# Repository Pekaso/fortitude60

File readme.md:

# Fortitude60

👊A 60% (12x5) split keyboard with staggerd column layout.👊

# Build Guide

## Fortitude60 v1.0(C94 Limited Edition)
[ビルドガイド（日本語）](Documents/buildguide_jp_v1.0.md)

[Build Guide (EN)](Documents/buildguide_en_v1.0.md)

## Fortitude60 v1.1(Yushakobo Ver.)
[ビルドガイド（日本語）](Documents/buildguide_jp_v1.1.md)

[Build Guide (EN)](Documents/buildguide_en_v1.1.md)

[Changes](https://github.com/Pekaso/fortitude60/issues/9)

# Firmware Flashing
[ファームウェア書き込み方法（日本語）](Documents/firmware_flashing-jp_new.md)

[Firmware Flashing（EN）](Documents/firmware_flashing-en_new.md)

## F.A.Q
[よくある質問（日本語）](Documents/faq_jp.md)

[Frequently Asked Questions（EN）](Documents/faq_en.md)

# License

Released under the MIT license. see [LICENSE](https://github.com/Pekaso/fortitude60/blob/master/LICENSE)

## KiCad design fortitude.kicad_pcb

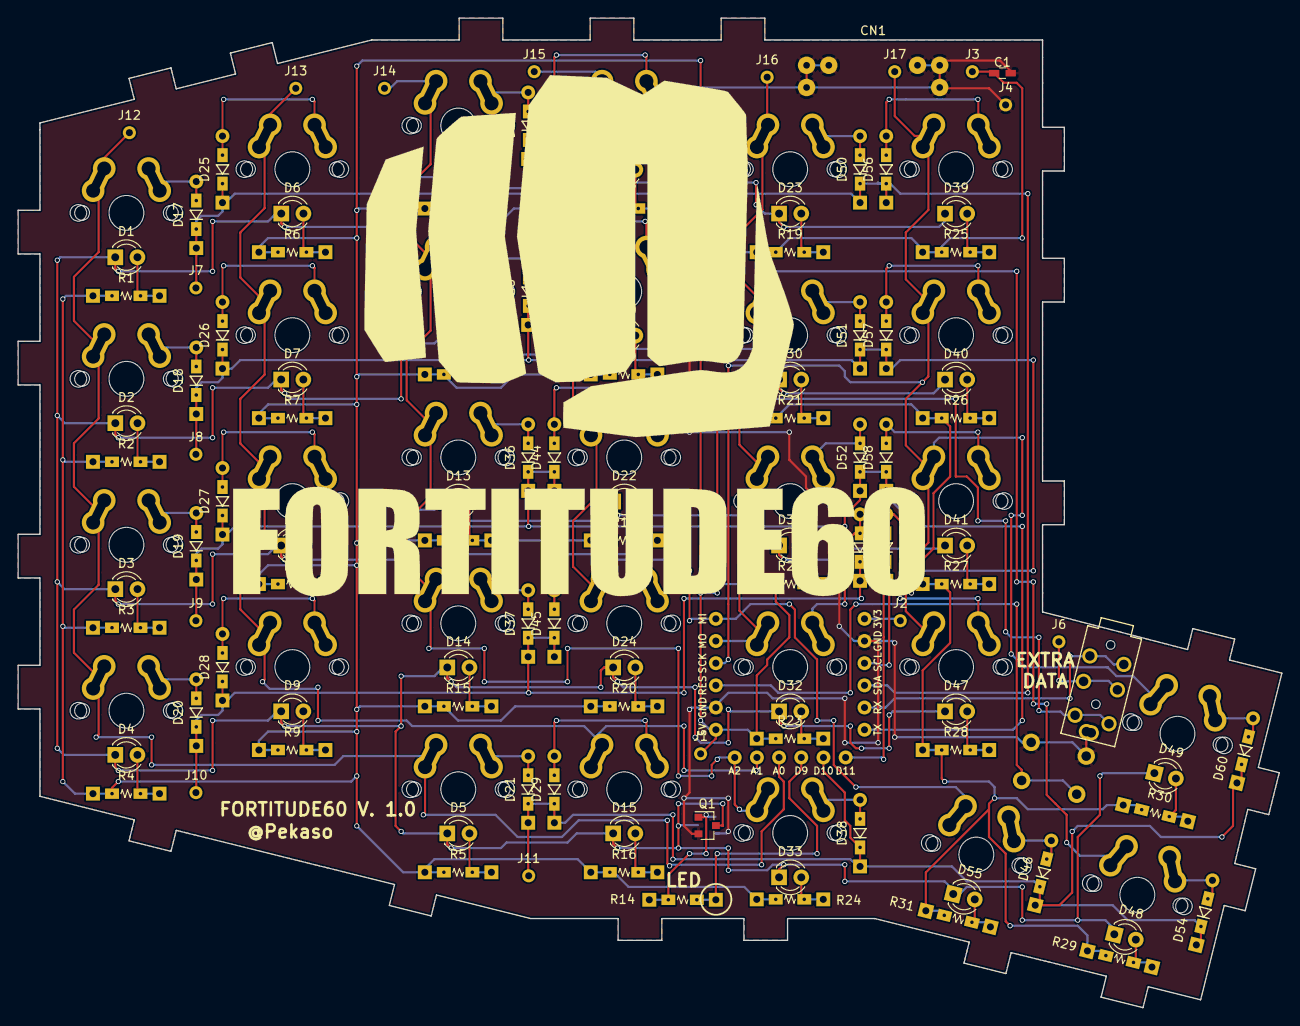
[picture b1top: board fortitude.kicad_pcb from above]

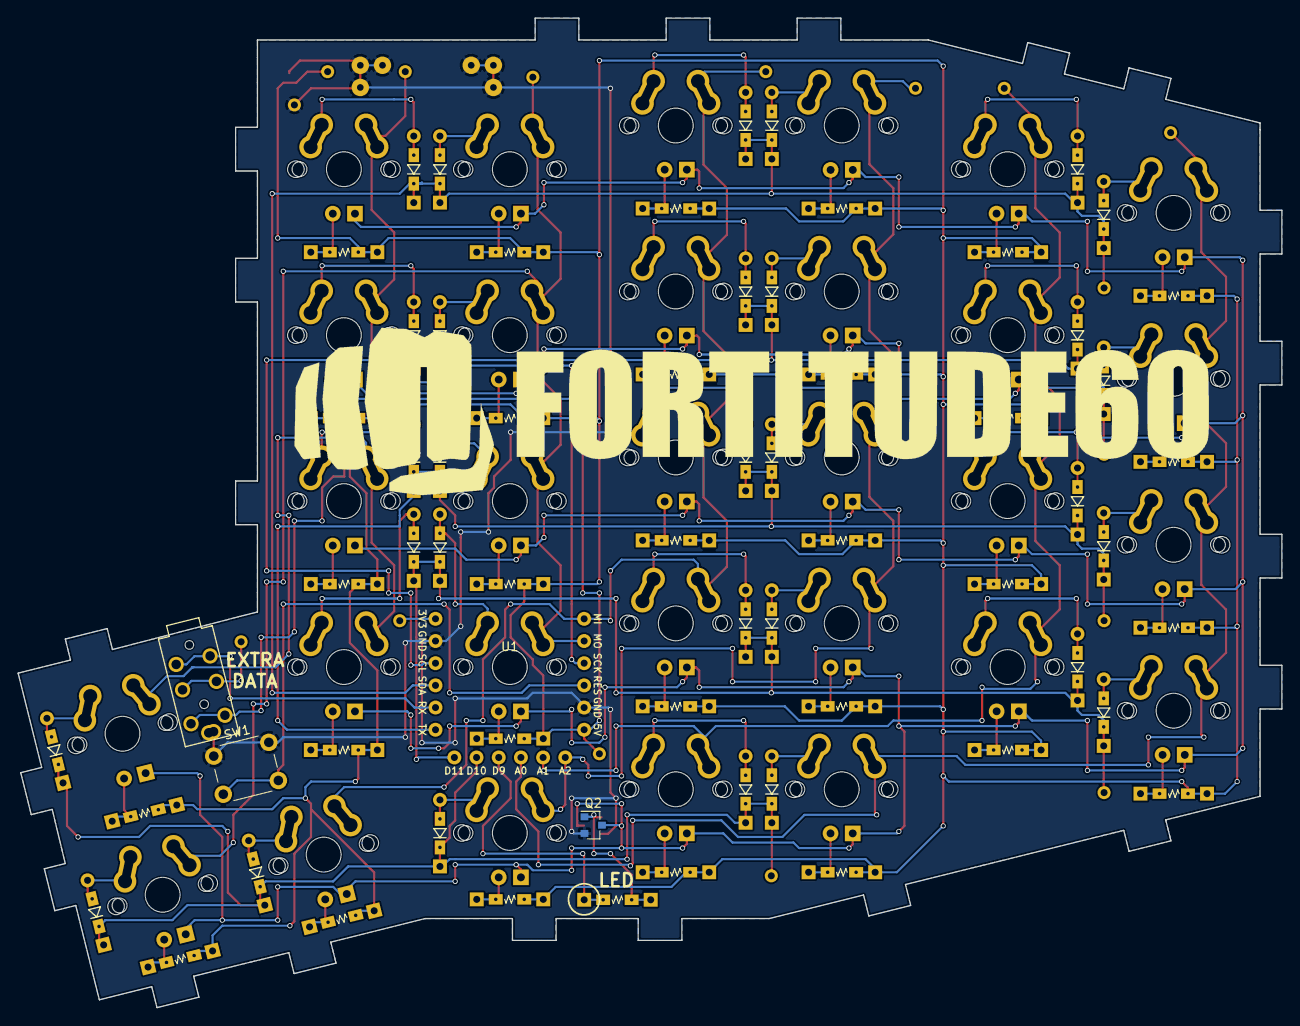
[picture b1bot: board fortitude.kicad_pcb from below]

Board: 2 copper layers, 144.7 x 113.3 mm, 144 parts (3 on the bottom side), 80 nets.

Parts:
C1: 0.1u; C_0603_HandSoldering
CN1: AE-USB2.0-TYPE-C-B
D1, D2, D3, D4, D5, D6, D7, D8, D9, D10, D11, D12, D13, D14, D15, D16, D22, D23, D24, D30, D31, D32, D33, D39, D40, D41, D47, D48, D49, D55: LED; LED_D3.0mm
D17, D18, D19, D20, D21, D25, D26, D27, D28, D29, D34, D35, D36, D37, D38, D42, D43, D44, D45, D46, D50, D51, D52, D53, D54, D56, D57, D58, D59, D60: 1N4148; Diode_SMD_THT_N
J1: 5V; Measurement_Point_Round-TH_Small
J2: 3V3; Measurement_Point_Round-TH_Small
J3: VBUS; Measurement_Point_Round-TH_Small
J4: GND; Measurement_Point_Round-TH_Small
J5: Audio-Jack-4; trrs_jack_r
J6: EX_DATA; Measurement_Point_Round-TH_Small
J7: ROW0; Measurement_Point_Round-TH_Small
J8: ROW1; Measurement_Point_Round-TH_Small
J9: ROW2; Measurement_Point_Round-TH_Small
J10: ROW3; Measurement_Point_Round-TH_Small
J11: ROW4; Measurement_Point_Round-TH_Small
J12: COL0; Measurement_Point_Round-TH_Small
J13: COL1; Measurement_Point_Round-TH_Small
J14: COL2; Measurement_Point_Round-TH_Small
J15: COL3; Measurement_Point_Round-TH_Small
J16: COL4; Measurement_Point_Round-TH_Small
J17: COL5; Measurement_Point_Round-TH_Small
Q1, Q2: IRLML6344TRPbF; SOT-23
R1, R2, R3, R4, R5, R6, R7, R8, R9, R10, R11, R12, R13, R15, R16, R17, R18, R19, R20, R21, R22, R23, R24, R25, R26, R27, R28, R29, R30, R31: 470; Resister_SMD_THT_N
R14: 1k; Resister_SMD_THT_N
SW1: RESET; SW_PUSH_6mm
SW2: SW_1_1; key_switch_mx
SW3: SW_1_2; key_switch_mx
SW4: SW_1_3; key_switch_mx
SW5: SW_1_4; key_switch_mx
SW6: SW_1_5; key_switch_mx
SW7: SW_2_1; key_switch_mx
SW8: SW_2_2; key_switch_mx
SW9: SW_2_3; key_switch_mx
SW10: SW_2_4; key_switch_mx
SW11: SW_2_5; key_switch_mx
SW12: SW_3_1; key_switch_mx
SW13: SW_3_2; key_switch_mx
SW14: SW_3_3; key_switch_mx
SW15: SW_3_4; key_switch_mx
SW16: SW_3_5; key_switch_mx
SW17: SW_4_1; key_switch_mx
SW18: SW_4_2; key_switch_mx
SW19: SW_4_3; key_switch_mx
SW20: SW_4_4; key_switch_mx
SW21: SW_4_5; key_switch_mx
SW22: SW_5_1; key_switch_mx
SW23: SW_5_2; key_switch_mx
SW24: SW_5_3; key_switch_mx
SW25: SW_5_4; key_switch_mx
SW26: SW_5_5; key_switch_mx
SW27: SW_6_1; key_switch_mx
SW28: SW_6_2; key_switch_mx
SW29: SW_6_3; key_switch_mx
SW30: SW_6_4; key_switch_mx
SW31: SW_6_5; key_switch_mx
U1: beetle

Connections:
COL1: J12.1, SW2.1, SW3.1, SW4.1, SW5.1, SW6.1, U1.10
COL2: J13.1, SW7.1, SW8.1, SW9.1, SW10.1, SW11.1, U1.11
COL3: J14.1, SW12.1, SW13.1, SW14.1, SW15.1, SW16.1, U1.12
COL4: J15.1, SW17.1, SW18.1, SW19.1, SW20.1, SW21.1, U1.18
COL5: J16.1, SW22.1, SW23.1, SW24.1, SW25.1, SW26.1, U1.17
COL6: J17.1, SW27.1, SW28.1, SW29.1, SW30.1, SW31.1, U1.16
GND: C1.2, CN1.1, J4.1, J5.4, Q1.2, Q2.2, SW1.1, U1.2, U1.14
LED: R14.2, U1.9
unnamed: D1.1, D2.1, D3.1, D4.1, D5.1, D6.1, D7.1, D8.1, D9.1, D10.1, D11.1, D12.1, D13.1, D14.1, D15.1, D16.1, D22.1, D23.1, D24.1, D30.1, D31.1, D32.1, D33.1, D39.1, D40.1, D41.1, D47.1, D48.1, D49.1, D55.1, Q1.3, Q2.3
unnamed: D1.2, R1.2
unnamed: D2.2, R2.2
unnamed: D3.2, R3.2
unnamed: D4.2, R4.2
unnamed: D5.2, R5.2
unnamed: D6.2, R6.2
unnamed: D7.2, R7.2
unnamed: D8.2, R8.2
unnamed: D9.2, R9.2
unnamed: D10.2, R10.2
unnamed: D11.2, R11.2
unnamed: D12.2, R12.2
unnamed: D13.2, R13.2
unnamed: D14.2, R15.2
unnamed: D15.2, R16.2
unnamed: D16.2, R17.2
unnamed: D17.2, SW2.2
unnamed: D18.2, SW3.2
unnamed: D19.2, SW4.2
unnamed: D20.2, SW5.2
unnamed: D21.2, SW6.2
unnamed: D22.2, R18.2
unnamed: D23.2, R19.2
unnamed: D24.2, R20.2
unnamed: D25.2, SW7.2
unnamed: D26.2, SW8.2
unnamed: D27.2, SW9.2
unnamed: D28.2, SW10.2
unnamed: D29.2, SW11.2
unnamed: D30.2, R21.2
unnamed: D31.2, R22.2
unnamed: D32.2, R23.2
unnamed: D33.2, R24.2
unnamed: D34.2, SW12.2
unnamed: D35.2, SW13.2
unnamed: D36.2, SW14.2
unnamed: D37.2, SW15.2
unnamed: D38.2, SW16.2
unnamed: D39.2, R25.2
unnamed: D40.2, R26.2
unnamed: D41.2, R27.2
unnamed: D42.2, SW17.2
unnamed: D43.2, SW18.2
unnamed: D44.2, SW19.2
unnamed: D45.2, SW20.2
unnamed: D46.2, SW21.2
unnamed: D47.2, R28.2
unnamed: D48.2, R29.2
unnamed: D49.2, R30.2
unnamed: D50.2, SW22.2
unnamed: D51.2, SW23.2
unnamed: D52.2, SW24.2
unnamed: D53.2, SW25.2
unnamed: D54.2, SW26.2
unnamed: D55.2, R31.2
unnamed: D56.2, SW27.2
unnamed: D57.2, SW28.2
unnamed: D58.2, SW29.2
unnamed: D59.2, SW30.2
unnamed: D60.2, SW31.2
unnamed: J2.1, U1.1
unnamed: J5.3, J6.1
unnamed: Q1.1, Q2.1, R14.1
unnamed: SW1.2, U1.15
ROW1: D17.1, D25.1, D34.1, D42.1, D50.1, D56.1, J7.1, U1.4
ROW2: D18.1, D26.1, D35.1, D43.1, D51.1, D57.1, J8.1, U1.3
ROW3: D19.1, D27.1, D36.1, D44.1, D52.1, D58.1, J9.1, U1.6
ROW4: D20.1, D28.1, D37.1, D45.1, D53.1, D59.1, J10.1, U1.7
ROW5: D21.1, D29.1, D38.1, D46.1, D54.1, D60.1, J11.1, U1.8
TXO: J5.2, U1.5
Vcc: C1.1, J1.1, J3.1, J5.1, R1.1, R2.1, R3.1, R4.1, R5.1, R6.1, R7.1, R8.1, R9.1, R10.1, R11.1, R12.1, R13.1, R15.1, R16.1, R17.1, R18.1, R19.1, R20.1, R21.1, R22.1, R23.1, R24.1, R25.1, R26.1, R27.1, R28.1, R29.1, R30.1, R31.1, U1.13

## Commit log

2018-06-11 add pcb data
2018-06-11 add case and readme
2018-06-11 add LICENSE
2018-06-11 modify LICENSE
2018-06-16 add build guide
2018-07-30 Add v1.0 Build Guide
2018-07-30 Add some image
2018-08-08 少し手直し
2018-08-11 一部画像の修正とUnderglowオプションに追記
2018-08-15 はずかしいミスを修正
2018-10-13 Add FAQ
2018-10-13 Add Type-C support
2018-10-24 add document for PCB v1.1 and above.
2018-10-24 Add the note for use the type-C to type-C cable.
2018-10-29 パーツの誤りを修正。
2019-01-19 Update buildguide_jp_v1.0.md
    QMKのファームでデフォルトではUndeglowが有効になってるのでQMKに合わせる
2019-03-07 add firmware flashing guide
2019-03-16 fix typo.
2019-03-18 add Yushakobo Ver.
2019-03-18 fix URL
2019-07-29 update main-PCB and plate data
2020-04-06 split_common対応
    split_commonが導入されたら右手側もそのまま認識されるようになったので対応
2020-08-23 * Added English build guides
2020-08-23 * More proper grammar
2020-08-24 * Translated FAQ
2020-08-24 * Added firmware flashing instructions
2020-08-24 * Fixed typos
2020-08-26 * Fixed whitespace error in file name
2021-11-24 Fix "PCB" typo
2021-11-24 Link to documented v1.1 changes
